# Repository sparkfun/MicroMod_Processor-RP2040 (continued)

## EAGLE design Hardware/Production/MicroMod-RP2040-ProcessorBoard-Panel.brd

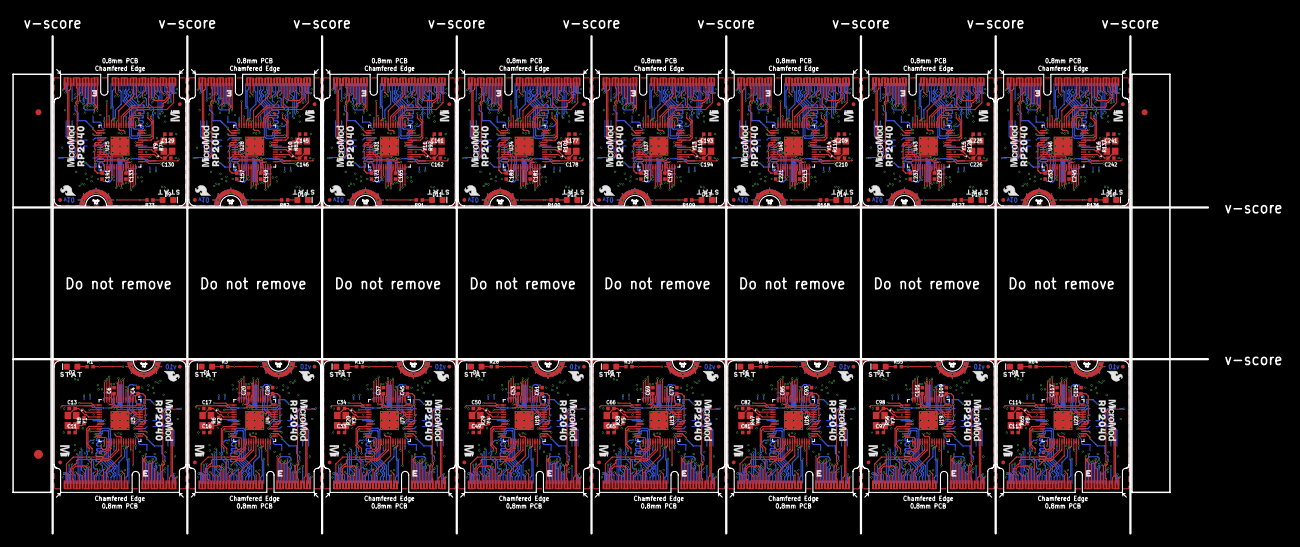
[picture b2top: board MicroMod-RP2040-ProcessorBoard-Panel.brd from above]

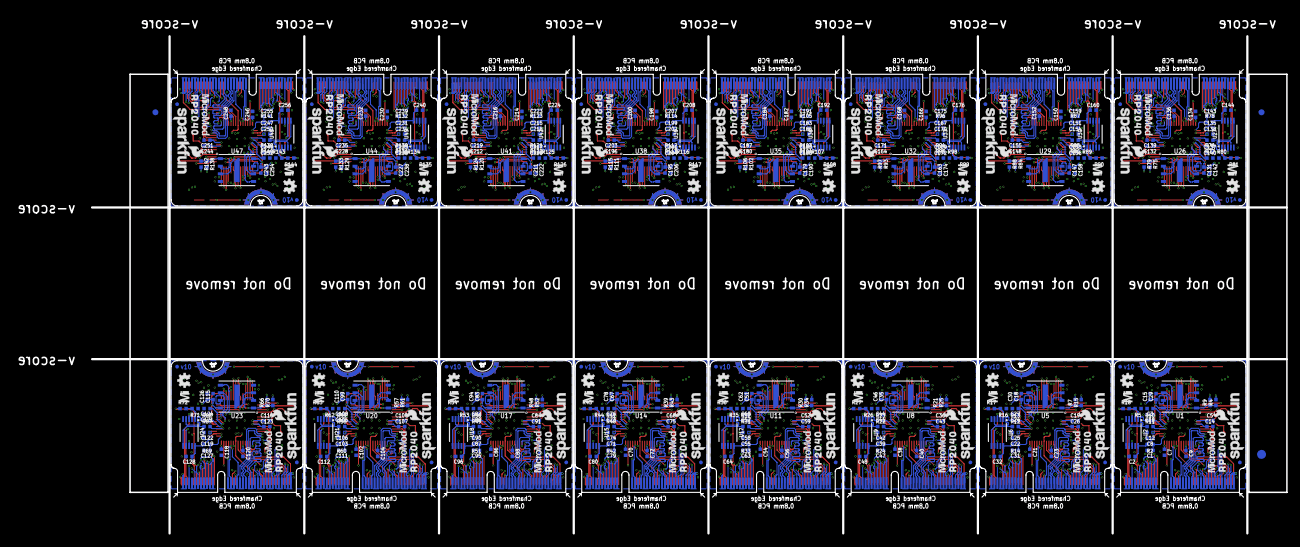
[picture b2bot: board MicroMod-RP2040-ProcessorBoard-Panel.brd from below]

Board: 4 copper layers, 199.6 x 83.1 mm, 726 parts (451 on the bottom side), 928 nets.

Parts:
C1, C3, C4, C15, C27, C28, C30, C31, C44, C45, C46, C47, C60, C61, C62, C63, C76, C77, C78, C79, C92, C93, C94, C95, C108, C109, C110, C111, C124, C125, C126, C127, C140, C141, C142, C143, C156, C157, C158, C159, C172, C173, C174, C175, C188, C189, C190, C191, C204, C205, C206, C207, C220, C221, C222, C223, C236, C237, C238, C239, C252, C253, C254, C255: 2.2uF; 0402-TIGHT
C2, C5, C6, C7, C8, C9, C10, C12, C14, C18, C19, C20, C21, C22, C23, C24, C25, C26, C29, C32, C35, C36, C37, C38, C39, C40, C41, C42, C43, C48, C51, C52, C53, C54, C55, C56, C57, C58, C59, C64, C67, C68, C69, C70, C71, C72, C73, C74, C75, C80, C83, C84, C85, C86, C87, C88, C89, C90, C91, C96, C99, C100, C101, C102, C103, C104, C105, C106, C107, C112, C115, C116, C117, C118, C119, C120, C121, C122, C123, C128, C131, C132, C133, C134, C135, C136, C137, C138, C139, C144, C147, C148, C149, C150, C151, C152, C153, C154, C155, C160, C163, C164, C165, C166, C167, C168, C169, C170, C171, C176, C179, C180, C181, C182, C183, C184, C185, C186, C187, C192, C195, C196, C197, C198, C199, C200, C201, C202, C203, C208, C211, C212, C213, C214, C215, C216, C217, C218, C219, C224, C227, C228, C229, C230, C231, C232, C233, C234, C235, C240, C243, C244, C245, C246, C247, C248, C249, C250, C251, C256: 0.1uF; 0402-TIGHT
C11, C13, C16, C17, C33, C34, C49, C50, C65, C66, C81, C82, C97, C98, C113, C114, C129, C130, C145, C146, C161, C162, C177, C178, C193, C194, C209, C210, C225, C226, C241, C242: 15pF; 0402-TIGHT
D1, D2, D3, D4, D5, D6, D7, D8, D9, D10, D11, D12, D13, D14, D15, D16: BLUE; LED-0603
E$1, E$2, E$3, E$4: FIDUCIAL-1X2
E$5, E$6: FIDUCIAL-1.5X3
FD1, FD2, FD3, FD4, FD5, FD6, FD7, FD8, FD9, FD10, FD11, FD12, FD13, FD14, FD15, FD16, FD17, FD18, FD19, FD20, FD21, FD22, FD23, FD24, FD25, FD26, FD27, FD28, FD29, FD30, FD31, FD32, FD33, FD34, FD35, FD36, FD37, FD38, FD39, FD40, FD41, FD42, FD43, FD44, FD45, FD46, FD47, FD48, FD49, FD50, FD51, FD52, FD53, FD54, FD55, FD56, FD57, FD58, FD59, FD60, FD61, FD62, FD63, FD64: FIDUCIALUFIDUCIAL; FIDUCIAL-MICRO
J1, J2, J3, J4, J5, J6, J7, J8, J9, J10, J11, J12, J13, J14, J15, J16: MICROMOD-2222; M.2-CARD-E-22
LOGO1, LOGO5, LOGO8, LOGO11, LOGO14, LOGO17, LOGO20, LOGO23, LOGO26, LOGO29, LOGO32, LOGO35, LOGO38, LOGO41, LOGO44, LOGO47: SFE_LOGO_NAME_FLAME.1_INCH; SFE_LOGO_NAME_FLAME_.1
LOGO2, LOGO6, LOGO9, LOGO12, LOGO15, LOGO18, LOGO21, LOGO24, LOGO27, LOGO30, LOGO33, LOGO36, LOGO39, LOGO42, LOGO45, LOGO48: SFE_LOGO_FLAME.1_INCH; SFE_LOGO_FLAME_.1
LOGO3, LOGO4, LOGO7, LOGO10, LOGO13, LOGO16, LOGO19, LOGO22, LOGO25, LOGO28, LOGO31, LOGO34, LOGO37, LOGO40, LOGO43, LOGO46: OSHW-LOGOMINI; OSHW-LOGO-MINI
R1, R3, R6, R7, R8, R9, R17, R18, R19, R20, R21, R27, R28, R29, R30, R36, R37, R38, R39, R45, R46, R47, R48, R54, R55, R56, R57, R63, R64, R65, R66, R72, R73, R74, R75, R81, R82, R83, R84, R90, R91, R92, R93, R99, R100, R101, R102, R108, R109, R110, R111, R117, R118, R119, R120, R126, R127, R128, R129, R135, R136, R137, R138, R144: 1k; 0402-TIGHT
R2, R14, R24, R33, R42, R51, R60, R69, R78, R87, R96, R105, R114, R123, R132, R141: 200OHM-0402T-1/16W-1%; 0402-TIGHT
R4, R5, R15, R16, R25, R26, R34, R35, R43, R44, R52, R53, R61, R62, R70, R71, R79, R80, R88, R89, R97, R98, R106, R107, R115, R116, R124, R125, R133, R134, R142, R143: 10k; 0402-TIGHT
R10, R11, R12, R13, R22, R23, R31, R32, R40, R41, R49, R50, R58, R59, R67, R68, R76, R77, R85, R86, R94, R95, R103, R104, R112, R113, R121, R122, R130, R131, R139, R140: 27; 0402-TIGHT
U1, U5, U8, U11, U14, U17, U20, U23, U26, U29, U32, U35, U38, U41, U44, U47: W25QXX128MBIT; WSON-8-6X5-SKINNY_CENTERPAD
U2, U6, U9, U12, U15, U18, U21, U24, U27, U30, U33, U36, U39, U42, U45, U48: FSUSB30MUX_MSOP10; MSOP10
U3, U4, U7, U10, U13, U16, U19, U22, U25, U28, U31, U34, U37, U40, U43, U46: RP2040; QFN-56
U$1, U$2, U$5, U$7, U$15, U$16, U$22, U$23, U$29, U$30, U$36, U$37, U$43, U$44, U$50, U$51, U$57, U$58, U$64, U$65, U$71, U$72, U$78, U$79, U$85, U$86, U$92, U$93, U$99, U$100, U$106, U$107: MICROMOD_MI_LOGO_.35
U$3, U$10, U$12, U$13, U$19, U$20, U$26, U$27, U$33, U$34, U$40, U$41, U$47, U$48, U$54, U$55, U$61, U$62, U$68, U$69, U$75, U$76, U$82, U$83, U$89, U$90, U$96, U$97, U$103, U$104, U$110, U$111: MICROMOD_LOGO_.3
U$4, U$8, U$9, U$14, U$18, U$21, U$25, U$28, U$32, U$35, U$39, U$42, U$46, U$49, U$53, U$56, U$60, U$63, U$67, U$70, U$74, U$77, U$81, U$84, U$88, U$91, U$95, U$98, U$102, U$105, U$109, U$112: RP20400
U$6, U$11, U$17, U$24, U$31, U$38, U$45, U$52, U$59, U$66, U$73, U$80, U$87, U$94, U$101, U$108: STAT0
Y1, Y2, Y3, Y4, Y5, Y6, Y7, Y8, Y9, Y10, Y11, Y12, Y13, Y14, Y15, Y16: 12MHz; CRYSTAL-SMD-2X2.5MM

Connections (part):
1.1V: C3.1, C12.1, C14.1, U3.23, U3.45, U3.50
1.1V1: C25.1, C26.1, C27.1, U4.23, U4.45, U4.50
1.1V2: C42.1, C43.1, C44.1, U7.23, U7.45, U7.50
1.1V3: C58.1, C59.1, C60.1, U10.23, U10.45, U10.50
1.1V4: C74.1, C75.1, C76.1, U13.23, U13.45, U13.50
1.1V5: C90.1, C91.1, C92.1, U16.23, U16.45, U16.50
1.1V6: C106.1, C107.1, C108.1, U19.23, U19.45, U19.50
1.1V7: C122.1, C123.1, C124.1, U22.23, U22.45, U22.50
1.1V8: C138.1, C139.1, C140.1, U25.23, U25.45, U25.50
1.1V9: C154.1, C155.1, C156.1, U28.23, U28.45, U28.50
1.1V10: C170.1, C171.1, C172.1, U31.23, U31.45, U31.50
1.1V11: C186.1, C187.1, C188.1, U34.23, U34.45, U34.50
1.1V12: C202.1, C203.1, C204.1, U37.23, U37.45, U37.50
1.1V13: C218.1, C219.1, C220.1, U40.23, U40.45, U40.50
1.1V14: C234.1, C235.1, C236.1, U43.23, U43.45, U43.50
1.1V15: C250.1, C251.1, C252.1, U46.23, U46.45, U46.50
3.3V: C2.1, C4.1, C5.1, C6.1, C7.1, C8.1, C9.1, C10.1, C15.1, C29.1, J1.2, J1.72, J1.74, R2.2, R4.2, U1.8, U2.10, U3.1, U3.10, U3.22, U3.33, U3.42, U3.44, U3.48, U3.49
3.3V1: C18.1, C19.1, C20.1, C21.1, C22.1, C23.1, C24.1, C28.1, C30.1, C32.1, J2.2, J2.72, J2.74, R14.2, R15.2, U4.1, U4.10, U4.22, U4.33, U4.42, U4.44, U4.48, U4.49, U5.8, U6.10
3.3V2: C35.1, C36.1, C37.1, C38.1, C39.1, C40.1, C41.1, C45.1, C46.1, C48.1, J3.2, J3.72, J3.74, R24.2, R25.2, U7.1, U7.10, U7.22, U7.33, U7.42, U7.44, U7.48, U7.49, U8.8, U9.10
3.3V3: C51.1, C52.1, C53.1, C54.1, C55.1, C56.1, C57.1, C61.1, C62.1, C64.1, J4.2, J4.72, J4.74, R33.2, R34.2, U10.1, U10.10, U10.22, U10.33, U10.42, U10.44, U10.48, U10.49, U11.8, U12.10
3.3V4: C67.1, C68.1, C69.1, C70.1, C71.1, C72.1, C73.1, C77.1, C78.1, C80.1, J5.2, J5.72, J5.74, R42.2, R43.2, U13.1, U13.10, U13.22, U13.33, U13.42, U13.44, U13.48, U13.49, U14.8, U15.10
3.3V5: C83.1, C84.1, C85.1, C86.1, C87.1, C88.1, C89.1, C93.1, C94.1, C96.1, J6.2, J6.72, J6.74, R51.2, R52.2, U16.1, U16.10, U16.22, U16.33, U16.42, U16.44, U16.48, U16.49, U17.8, U18.10
3.3V6: C99.1, C100.1, C101.1, C102.1, C103.1, C104.1, C105.1, C109.1, C110.1, C112.1, J7.2, J7.72, J7.74, R60.2, R61.2, U19.1, U19.10, U19.22, U19.33, U19.42, U19.44, U19.48, U19.49, U20.8, U21.10
3.3V7: C115.1, C116.1, C117.1, C118.1, C119.1, C120.1, C121.1, C125.1, C126.1, C128.1, J8.2, J8.72, J8.74, R69.2, R70.2, U22.1, U22.10, U22.22, U22.33, U22.42, U22.44, U22.48, U22.49, U23.8, U24.10
3.3V8: C131.1, C132.1, C133.1, C134.1, C135.1, C136.1, C137.1, C141.1, C142.1, C144.1, J9.2, J9.72, J9.74, R78.2, R79.2, U25.1, U25.10, U25.22, U25.33, U25.42, U25.44, U25.48, U25.49, U26.8, U27.10
3.3V9: C147.1, C148.1, C149.1, C150.1, C151.1, C152.1, C153.1, C157.1, C158.1, C160.1, J10.2, J10.72, J10.74, R87.2, R88.2, U28.1, U28.10, U28.22, U28.33, U28.42, U28.44, U28.48, U28.49, U29.8, U30.10
3.3V10: C163.1, C164.1, C165.1, C166.1, C167.1, C168.1, C169.1, C173.1, C174.1, C176.1, J11.2, J11.72, J11.74, R96.2, R97.2, U31.1, U31.10, U31.22, U31.33, U31.42, U31.44, U31.48, U31.49, U32.8, U33.10
3.3V11: C179.1, C180.1, C181.1, C182.1, C183.1, C184.1, C185.1, C189.1, C190.1, C192.1, J12.2, J12.72, J12.74, R105.2, R106.2, U34.1, U34.10, U34.22, U34.33, U34.42, U34.44, U34.48, U34.49, U35.8, U36.10
3.3V12: C195.1, C196.1, C197.1, C198.1, C199.1, C200.1, C201.1, C205.1, C206.1, C208.1, J13.2, J13.72, J13.74, R114.2, R115.2, U37.1, U37.10, U37.22, U37.33, U37.42, U37.44, U37.48, U37.49, U38.8, U39.10
3.3V13: C211.1, C212.1, C213.1, C214.1, C215.1, C216.1, C217.1, C221.1, C222.1, C224.1, J14.2, J14.72, J14.74, R123.2, R124.2, U40.1, U40.10, U40.22, U40.33, U40.42, U40.44, U40.48, U40.49, U41.8, U42.10
3.3V14: C227.1, C228.1, C229.1, C230.1, C231.1, C232.1, C233.1, C237.1, C238.1, C240.1, J15.2, J15.72, J15.74, R132.2, R133.2, U43.1, U43.10, U43.22, U43.33, U43.42, U43.44, U43.48, U43.49, U44.8, U45.10
3.3V15: C243.1, C244.1, C245.1, C246.1, C247.1, C248.1, C249.1, C253.1, C254.1, C256.1, J16.2, J16.72, J16.74, R141.2, R142.2, U46.1, U46.10, U46.22, U46.33, U46.42, U46.44, U46.48, U46.49, U47.8, U48.10
!RESET!: J1.6, U3.26
!RESET!1: J2.6, U4.26
!RESET!2: J3.6, U7.26
!RESET!3: J4.6, U10.26
!RESET!4: J5.6, U13.26
!RESET!5: J6.6, U16.26
!RESET!6: J7.6, U19.26
!RESET!7: J8.6, U22.26
!RESET!8: J9.6, U25.26
!RESET!9: J10.6, U28.26
!RESET!10: J11.6, U31.26
!RESET!11: J12.6, U34.26
!RESET!12: J13.6, U37.26
!RESET!13: J14.6, U40.26
!RESET!14: J15.6, U43.26
!RESET!15: J16.6, U46.26
ADC0: J1.34, U3.38
ADC1: J1.38, U3.39
ADC2: J2.34, U4.38
ADC3: J2.38, U4.39
ADC4: J3.34, U7.38
ADC5: J3.38, U7.39
ADC6: J4.34, U10.38
ADC7: J4.38, U10.39
ADC8: J5.34, U13.38
ADC9: J5.38, U13.39
ADC10: J6.34, U16.38
ADC11: J6.38, U16.39
ADC12: J7.34, U19.38
ADC13: J7.38, U19.39
ADC14: J8.34, U22.38
ADC15: J8.38, U22.39
ADC16: J9.34, U25.38
ADC17: J9.38, U25.39
ADC18: J10.34, U28.38
ADC19: J10.38, U28.39
ADC20: J11.34, U31.38
ADC21: J11.38, U31.39
ADC22: J12.34, U34.38
ADC23: J12.38, U34.39
ADC24: J13.34, U37.38
ADC25: J13.38, U37.39
ADC26: J14.34, U40.38
ADC27: J14.38, U40.39
ADC28: J15.34, U43.38
ADC29: J15.38, U43.39
ADC30: J16.34, U46.38
ADC31: J16.38, U46.39
ADC_VDD: C1.1, R2.1, U3.43
ADC_VDD1: C31.1, R14.1, U4.43
ADC_VDD2: C47.1, R24.1, U7.43
ADC_VDD3: C63.1, R33.1, U10.43
ADC_VDD4: C79.1, R42.1, U13.43
ADC_VDD5: C95.1, R51.1, U16.43
ADC_VDD6: C111.1, R60.1, U19.43
ADC_VDD7: C127.1, R69.1, U22.43
ADC_VDD8: C143.1, R78.1, U25.43
ADC_VDD9: C159.1, R87.1, U28.43
ADC_VDD10: C175.1, R96.1, U31.43
ADC_VDD11: C191.1, R105.1, U34.43
ADC_VDD12: C207.1, R114.1, U37.43
ADC_VDD13: C223.1, R123.1, U40.43
ADC_VDD14: C239.1, R132.1, U43.43
ADC_VDD15: C255.1, R141.1, U46.43
BATT_VIN/1: J2.49, U4.41
BATT_VIN/2: J3.49, U7.41
BATT_VIN/3: J1.49, U3.41
BATT_VIN/4: J4.49, U10.41
BATT_VIN/5: J5.49, U13.41
BATT_VIN/6: J6.49, U16.41
BATT_VIN/7: J7.49, U19.41
BATT_VIN/8: J8.49, U22.41
BATT_VIN/9: J9.49, U25.41
BATT_VIN/10: J10.49, U28.41
BATT_VIN/11: J11.49, U31.41
BATT_VIN/12: J12.49, U34.41
BATT_VIN/13: J13.49, U37.41
BATT_VIN/14: J14.49, U40.41
BATT_VIN/15: J15.49, U43.41
BATT_VIN/16: J16.49, U46.41
BOOT: J1.11, R9.2
BOOT1: J2.11, R7.2
BOOT2: J3.11, R21.2
BOOT3: J4.11, R30.2
BOOT4: J5.11, R39.2
BOOT5: J6.11, R48.2
BOOT6: J7.11, R57.2
BOOT7: J8.11, R66.2
BOOT8: J9.11, R75.2
BOOT9: J10.11, R84.2
BOOT10: J11.11, R93.2
BOOT11: J12.11, R102.2
BOOT12: J13.11, R111.2
BOOT13: J14.11, R120.2
BOOT14: J15.11, R129.2
BOOT15: J16.11, R138.2
CTS1/AUD_LRCLK: J1.15, J1.52, U3.4
CTS1/AUD_LRCLK1: J2.15, J2.52, U4.4
CTS1/AUD_LRCLK2: J3.15, J3.52, U7.4
CTS1/AUD_LRCLK3: J4.15, J4.52, U10.4
CTS1/AUD_LRCLK4: J5.15, J5.52, U13.4
CTS1/AUD_LRCLK5: J6.15, J6.52, U16.4
CTS1/AUD_LRCLK6: J7.15, J7.52, U19.4
CTS1/AUD_LRCLK7: J8.15, J8.52, U22.4
CTS1/AUD_LRCLK8: J9.15, J9.52, U25.4
CTS1/AUD_LRCLK9: J10.15, J10.52, U28.4
CTS1/AUD_LRCLK10: J11.15, J11.52, U31.4
CTS1/AUD_LRCLK11: J12.15, J12.52, U34.4
CTS1/AUD_LRCLK12: J13.15, J13.52, U37.4
CTS1/AUD_LRCLK13: J14.15, J14.52, U40.4
CTS1/AUD_LRCLK14: J15.15, J15.52, U43.4
CTS1/AUD_LRCLK15: J16.15, J16.52, U46.4
D0: J1.10, U3.8
D1: J1.18, U3.9
D2: J2.10, U4.8
D3: J2.18, U4.9
D4: J3.10, U7.8
D5: J3.18, U7.9
D6: J4.10, U10.8
D7: J4.18, U10.9
D8: J5.10, U13.8
D9: J5.18, U13.9
D10: J6.10, U16.8
D11: J6.18, U16.9
D12: J7.10, U19.8
D13: J7.18, U19.9
D14: J8.10, U22.8
D15: J8.18, U22.9
D16: J9.10, U25.8
D17: J9.18, U25.9
D18: J10.10, U28.8
D19: J10.18, U28.9
D20: J11.10, U31.8
D21: J11.18, U31.9
D22: J12.10, U34.8
D23: J12.18, U34.9
D24: J13.10, U37.8
D25: J13.18, U37.9
D26: J14.10, U40.8
D27: J14.18, U40.9
D28: J15.10, U43.8
D29: J15.18, U43.9
D30: J16.10, U46.8
D31: J16.18, U46.9
GND: C1.2, C2.2, C3.2, C4.2, C5.2, C6.2, C7.2, C8.2, C9.2, C10.2, C11.1, C12.2, C13.1, C14.2, C15.2, C29.2, D2.C, J1.1, J1.7, J1.33, J1.36, J1.39, J1.45, J1.75, J1.GND1, J1.GND2, J1.GND3, R5.1, U1.4, U2.5, U2.9, U3.19, U3.EPAD
GND1: C16.1, C17.1, C18.2, C19.2, C20.2, C21.2, C22.2, C23.2, C24.2, C25.2, C26.2, C27.2, C28.2, C30.2, C31.2, C32.2, D1.C, J2.1, J2.7, J2.33, J2.36, J2.39, J2.45, J2.75, J2.GND1, J2.GND2, J2.GND3, R16.1, U4.19, U4.EPAD, U5.4, U6.5, U6.9
GND2: C33.1, C34.1, C35.2, C36.2, C37.2, C38.2, C39.2, C40.2, C41.2, C42.2, C43.2, C44.2, C45.2, C46.2, C47.2, C48.2, D3.C, J3.1, J3.7, J3.33, J3.36, J3.39, J3.45, J3.75, J3.GND1, J3.GND2, J3.GND3, R26.1, U7.19, U7.EPAD, U8.4, U9.5, U9.9
GND3: C49.1, C50.1, C51.2, C52.2, C53.2, C54.2, C55.2, C56.2, C57.2, C58.2, C59.2, C60.2, C61.2, C62.2, C63.2, C64.2, D4.C, J4.1, J4.7, J4.33, J4.36, J4.39, J4.45, J4.75, J4.GND1, J4.GND2, J4.GND3, R35.1, U10.19, U10.EPAD, U11.4, U12.5, U12.9
GND4: C65.1, C66.1, C67.2, C68.2, C69.2, C70.2, C71.2, C72.2, C73.2, C74.2, C75.2, C76.2, C77.2, C78.2, C79.2, C80.2, D5.C, J5.1, J5.7, J5.33, J5.36, J5.39, J5.45, J5.75, J5.GND1, J5.GND2, J5.GND3, R44.1, U13.19, U13.EPAD, U14.4, U15.5, U15.9
GND5: C81.1, C82.1, C83.2, C84.2, C85.2, C86.2, C87.2, C88.2, C89.2, C90.2, C91.2, C92.2, C93.2, C94.2, C95.2, C96.2, D6.C, J6.1, J6.7, J6.33, J6.36, J6.39, J6.45, J6.75, J6.GND1, J6.GND2, J6.GND3, R53.1, U16.19, U16.EPAD, U17.4, U18.5, U18.9
GND6: C97.1, C98.1, C99.2, C100.2, C101.2, C102.2, C103.2, C104.2, C105.2, C106.2, C107.2, C108.2, C109.2, C110.2, C111.2, C112.2, D7.C, J7.1, J7.7, J7.33, J7.36, J7.39, J7.45, J7.75, J7.GND1, J7.GND2, J7.GND3, R62.1, U19.19, U19.EPAD, U20.4, U21.5, U21.9
GND7: C113.1, C114.1, C115.2, C116.2, C117.2, C118.2, C119.2, C120.2, C121.2, C122.2, C123.2, C124.2, C125.2, C126.2, C127.2, C128.2, D8.C, J8.1, J8.7, J8.33, J8.36, J8.39, J8.45, J8.75, J8.GND1, J8.GND2, J8.GND3, R71.1, U22.19, U22.EPAD, U23.4, U24.5, U24.9
GND8: C129.1, C130.1, C131.2, C132.2, C133.2, C134.2, C135.2, C136.2, C137.2, C138.2, C139.2, C140.2, C141.2, C142.2, C143.2, C144.2, D9.C, J9.1, J9.7, J9.33, J9.36, J9.39, J9.45, J9.75, J9.GND1, J9.GND2, J9.GND3, R80.1, U25.19, U25.EPAD, U26.4, U27.5, U27.9
GND9: C145.1, C146.1, C147.2, C148.2, C149.2, C150.2, C151.2, C152.2, C153.2, C154.2, C155.2, C156.2, C157.2, C158.2, C159.2, C160.2, D10.C, J10.1, J10.7, J10.33, J10.36, J10.39, J10.45, J10.75, J10.GND1, J10.GND2, J10.GND3, R89.1, U28.19, U28.EPAD, U29.4, U30.5, U30.9
GND10: C161.1, C162.1, C163.2, C164.2, C165.2, C166.2, C167.2, C168.2, C169.2, C170.2, C171.2, C172.2, C173.2, C174.2, C175.2, C176.2, D11.C, J11.1, J11.7, J11.33, J11.36, J11.39, J11.45, J11.75, J11.GND1, J11.GND2, J11.GND3, R98.1, U31.19, U31.EPAD, U32.4, U33.5, U33.9
GND11: C177.1, C178.1, C179.2, C180.2, C181.2, C182.2, C183.2, C184.2, C185.2, C186.2, C187.2, C188.2, C189.2, C190.2, C191.2, C192.2, D12.C, J12.1, J12.7, J12.33, J12.36, J12.39, J12.45, J12.75, J12.GND1, J12.GND2, J12.GND3, R107.1, U34.19, U34.EPAD, U35.4, U36.5, U36.9
GND12: C193.1, C194.1, C195.2, C196.2, C197.2, C198.2, C199.2, C200.2, C201.2, C202.2, C203.2, C204.2, C205.2, C206.2, C207.2, C208.2, D13.C, J13.1, J13.7, J13.33, J13.36, J13.39, J13.45, J13.75, J13.GND1, J13.GND2, J13.GND3, R116.1, U37.19, U37.EPAD, U38.4, U39.5, U39.9
GND13: C209.1, C210.1, C211.2, C212.2, C213.2, C214.2, C215.2, C216.2, C217.2, C218.2, C219.2, C220.2, C221.2, C222.2, C223.2, C224.2, D14.C, J14.1, J14.7, J14.33, J14.36, J14.39, J14.45, J14.75, J14.GND1, J14.GND2, J14.GND3, R125.1, U40.19, U40.EPAD, U41.4, U42.5, U42.9
GND14: C225.1, C226.1, C227.2, C228.2, C229.2, C230.2, C231.2, C232.2, C233.2, C234.2, C235.2, C236.2, C237.2, C238.2, C239.2, C240.2, D15.C, J15.1, J15.7, J15.33, J15.36, J15.39, J15.45, J15.75, J15.GND1, J15.GND2, J15.GND3, R134.1, U43.19, U43.EPAD, U44.4, U45.5, U45.9
GND15: C241.1, C242.1, C243.2, C244.2, C245.2, C246.2, C247.2, C248.2, C249.2, C250.2, C251.2, C252.2, C253.2, C254.2, C255.2, C256.2, D16.C, J16.1, J16.7, J16.33, J16.36, J16.39, J16.45, J16.75, J16.GND1, J16.GND2, J16.GND3, R143.1, U46.19, U46.EPAD, U47.4, U48.5, U48.9
GPIO0: J1.40, U3.27
GPIO1: J1.42, U3.28
GPIO2: J1.44, U3.29
GPIO3: J1.46, U3.30
GPIO4: J2.42, U4.28
GPIO5: J2.46, U4.30
GPIO6: J2.44, U4.29
GPIO7: J2.40, U4.27
GPIO8: J2.65, U4.40
GPIO9: J1.65, U3.40
GPIO10: J3.42, U7.28
GPIO11: J3.46, U7.30
GPIO12: J3.44, U7.29
GPIO13: J3.40, U7.27
GPIO14: J3.65, U7.40
GPIO15: J4.42, U10.28
GPIO16: J4.46, U10.30
GPIO17: J4.44, U10.29
GPIO18: J4.40, U10.27
GPIO19: J4.65, U10.40
GPIO20: J5.42, U13.28
GPIO21: J5.46, U13.30
GPIO22: J5.44, U13.29
GPIO23: J5.40, U13.27
GPIO24: J5.65, U13.40
GPIO25: J6.42, U16.28
GPIO26: J6.46, U16.30
GPIO27: J6.44, U16.29
GPIO28: J6.40, U16.27
GPIO29: J6.65, U16.40
GPIO30: J7.42, U19.28
GPIO31: J7.46, U19.30
GPIO32: J7.44, U19.29
GPIO33: J7.40, U19.27
GPIO34: J7.65, U19.40
GPIO35: J8.42, U22.28
GPIO36: J8.46, U22.30
GPIO37: J8.44, U22.29
GPIO38: J8.40, U22.27
GPIO39: J8.65, U22.40
GPIO40: J9.42, U25.28
GPIO41: J9.46, U25.30
GPIO42: J9.44, U25.29
GPIO43: J9.40, U25.27
GPIO44: J9.65, U25.40
GPIO45: J10.42, U28.28
GPIO46: J10.46, U28.30
GPIO47: J10.44, U28.29
GPIO48: J10.40, U28.27
GPIO49: J10.65, U28.40
GPIO50: J11.42, U31.28
GPIO51: J11.46, U31.30
GPIO52: J11.44, U31.29
GPIO53: J11.40, U31.27
GPIO54: J11.65, U31.40
GPIO55: J12.42, U34.28
GPIO56: J12.46, U34.30
GPIO57: J12.44, U34.29
GPIO58: J12.40, U34.27
GPIO59: J12.65, U34.40
GPIO60: J13.42, U37.28
GPIO61: J13.46, U37.30
GPIO62: J13.44, U37.29
GPIO63: J13.40, U37.27
GPIO64: J13.65, U37.40
GPIO65: J14.42, U40.28
GPIO66: J14.46, U40.30
GPIO67: J14.44, U40.29
GPIO68: J14.40, U40.27
GPIO69: J14.65, U40.40
GPIO70: J15.42, U43.28
GPIO71: J15.46, U43.30
GPIO72: J15.44, U43.29
GPIO73: J15.40, U43.27
GPIO74: J15.65, U43.40
GPIO75: J16.42, U46.28
GPIO76: J16.46, U46.30
GPIO77: J16.44, U46.29
GPIO78: J16.40, U46.27
GPIO79: J16.65, U46.40
I2C_!INT!/TX1: J2.16, J2.22, U4.11
I2C_!INT!/TX2: J1.16, J1.22, U3.11
I2C_!INT!/TX3: J3.16, J3.22, U7.11
I2C_!INT!/TX4: J4.16, J4.22, U10.11
I2C_!INT!/TX5: J5.16, J5.22, U13.11
I2C_!INT!/TX6: J6.16, J6.22, U16.11
I2C_!INT!/TX7: J7.16, J7.22, U19.11
I2C_!INT!/TX8: J8.16, J8.22, U22.11
I2C_!INT!/TX9: J9.16, J9.22, U25.11
I2C_!INT!/TX10: J10.16, J10.22, U28.11
I2C_!INT!/TX11: J11.16, J11.22, U31.11
I2C_!INT!/TX12: J12.16, J12.22, U34.11
I2C_!INT!/TX13: J13.16, J13.22, U37.11
I2C_!INT!/TX14: J14.16, J14.22, U40.11
I2C_!INT!/TX15: J15.16, J15.22, U43.11
I2C_!INT!/TX16: J16.16, J16.22, U46.11
LED_BUILTIN/G1: J2.63, R3.2, U4.37
LED_BUILTIN/G2: J3.63, R19.2, U7.37
LED_BUILTIN/G3: J4.63, R28.2, U10.37
LED_BUILTIN/G4: J5.63, R37.2, U13.37
LED_BUILTIN/G5: J6.63, R46.2, U16.37
LED_BUILTIN/G6: J7.63, R55.2, U19.37
LED_BUILTIN/G7: J8.63, R64.2, U22.37
LED_BUILTIN/G8: J9.63, R73.2, U25.37
LED_BUILTIN/G9: J10.63, R82.2, U28.37
LED_BUILTIN/G10: J1.63, R1.2, U3.37
LED_BUILTIN/G11: J11.63, R91.2, U31.37
LED_BUILTIN/G12: J12.63, R100.2, U34.37
LED_BUILTIN/G13: J13.63, R109.2, U37.37
LED_BUILTIN/G14: J14.63, R118.2, U40.37
LED_BUILTIN/G15: J15.63, R127.2, U43.37
LED_BUILTIN/G16: J16.63, R136.2, U46.37
unnamed: D1.A, R3.1
unnamed: D2.A, R1.1
unnamed: R6.2, U4.21
unnamed: R8.2, U3.21
unnamed: C13.2, U3.20, Y1.P3
unnamed: C11.2, R8.1, Y1.P1
unnamed: C17.2, U4.20, Y2.P3
unnamed: C16.2, R6.1, Y2.P1
unnamed: D3.A, R19.1
unnamed: R20.2, U7.21
unnamed: C34.2, U7.20, Y3.P3
unnamed: C33.2, R20.1, Y3.P1
unnamed: D4.A, R28.1
unnamed: R29.2, U10.21
unnamed: C50.2, U10.20, Y4.P3
unnamed: C49.2, R29.1, Y4.P1
unnamed: D5.A, R37.1
unnamed: R38.2, U13.21
unnamed: C66.2, U13.20, Y5.P3
unnamed: C65.2, R38.1, Y5.P1
unnamed: D6.A, R46.1
unnamed: R47.2, U16.21
unnamed: C82.2, U16.20, Y6.P3
unnamed: C81.2, R47.1, Y6.P1
unnamed: D7.A, R55.1
unnamed: R56.2, U19.21
unnamed: C98.2, U19.20, Y7.P3
unnamed: C97.2, R56.1, Y7.P1
unnamed: D8.A, R64.1
unnamed: R65.2, U22.21
unnamed: C114.2, U22.20, Y8.P3
unnamed: C113.2, R65.1, Y8.P1
unnamed: D9.A, R73.1
unnamed: R74.2, U25.21
unnamed: C130.2, U25.20, Y9.P3
unnamed: C129.2, R74.1, Y9.P1
unnamed: D10.A, R82.1
unnamed: R83.2, U28.21
unnamed: C146.2, U28.20, Y10.P3
unnamed: C145.2, R83.1, Y10.P1
unnamed: D11.A, R91.1
unnamed: R92.2, U31.21
unnamed: C162.2, U31.20, Y11.P3
unnamed: C161.2, R92.1, Y11.P1
unnamed: D12.A, R100.1
unnamed: R101.2, U34.21
unnamed: C178.2, U34.20, Y12.P3
unnamed: C177.2, R101.1, Y12.P1
unnamed: D13.A, R109.1
unnamed: R110.2, U37.21
unnamed: C194.2, U37.20, Y13.P3
unnamed: C193.2, R110.1, Y13.P1
unnamed: D14.A, R118.1
unnamed: R119.2, U40.21
unnamed: C210.2, U40.20, Y14.P3
unnamed: C209.2, R119.1, Y14.P1
unnamed: D15.A, R127.1
unnamed: R128.2, U43.21
unnamed: C226.2, U43.20, Y15.P3
unnamed: C225.2, R128.1, Y15.P1
unnamed: D16.A, R136.1
unnamed: R137.2, U46.21
unnamed: C242.2, U46.20, Y16.P3
unnamed: C241.2, R137.1, Y16.P1
PWM0: J1.32, U3.16
PWM1: J2.32, U4.16
PWM1/AUD_MCLK: J1.47, J1.58, U3.36
PWM1/AUD_MCLK1: J2.47, J2.58, U4.36
PWM1/AUD_MCLK2: J3.47, J3.58, U7.36
PWM1/AUD_MCLK3: J4.47, J4.58, U10.36
PWM1/AUD_MCLK4: J5.47, J5.58, U13.36
PWM1/AUD_MCLK5: J6.47, J6.58, U16.36
PWM1/AUD_MCLK6: J7.47, J7.58, U19.36
PWM1/AUD_MCLK7: J8.47, J8.58, U22.36
PWM1/AUD_MCLK8: J9.47, J9.58, U25.36
PWM1/AUD_MCLK9: J10.47, J10.58, U28.36
PWM1/AUD_MCLK10: J11.47, J11.58, U31.36
PWM1/AUD_MCLK11: J12.47, J12.58, U34.36
PWM1/AUD_MCLK12: J13.47, J13.58, U37.36
PWM1/AUD_MCLK13: J14.47, J14.58, U40.36
PWM1/AUD_MCLK14: J15.47, J15.58, U43.36
PWM1/AUD_MCLK15: J16.47, J16.58, U46.36
PWM2: J3.32, U7.16
PWM3: J4.32, U10.16
PWM4: J5.32, U13.16
PWM5: J6.32, U16.16
PWM6: J7.32, U19.16
PWM7: J8.32, U22.16
PWM8: J9.32, U25.16
PWM9: J10.32, U28.16
PWM10: J11.32, U31.16
PWM11: J12.32, U34.16
PWM12: J13.32, U37.16
PWM13: J14.32, U40.16
PWM14: J15.32, U43.16
PWM15: J16.32, U46.16
QSPI-0: U1.5, U3.53
QSPI-1: U1.2, U3.55
QSPI-2: U1.3, U3.54
QSPI-3: U1.7, U3.51
QSPI-4: U4.53, U5.5
QSPI-5: U4.51, U5.7
QSPI-6: U4.55, U5.2
QSPI-7: U4.54, U5.3
QSPI-8: U7.53, U8.5
QSPI-9: U7.51, U8.7
QSPI-10: U7.55, U8.2
QSPI-11: U7.54, U8.3
QSPI-12: U10.53, U11.5
QSPI-13: U10.51, U11.7
QSPI-14: U10.55, U11.2
QSPI-15: U10.54, U11.3
QSPI-16: U13.53, U14.5
QSPI-17: U13.51, U14.7
QSPI-18: U13.55, U14.2
QSPI-19: U13.54, U14.3
QSPI-20: U16.53, U17.5
QSPI-21: U16.51, U17.7
QSPI-22: U16.55, U17.2
QSPI-23: U16.54, U17.3
QSPI-24: U19.53, U20.5
QSPI-25: U19.51, U20.7
QSPI-26: U19.55, U20.2
QSPI-27: U19.54, U20.3
QSPI-28: U22.53, U23.5
QSPI-29: U22.51, U23.7
QSPI-30: U22.55, U23.2
QSPI-31: U22.54, U23.3
QSPI-32: U25.53, U26.5
QSPI-33: U25.51, U26.7
QSPI-34: U25.55, U26.2
QSPI-35: U25.54, U26.3
QSPI-36: U28.53, U29.5
QSPI-37: U28.51, U29.7
QSPI-38: U28.55, U29.2
QSPI-39: U28.54, U29.3
QSPI-40: U31.53, U32.5
QSPI-41: U31.51, U32.7
QSPI-42: U31.55, U32.2
QSPI-43: U31.54, U32.3
QSPI-44: U34.53, U35.5
QSPI-45: U34.51, U35.7
QSPI-46: U34.55, U35.2
QSPI-47: U34.54, U35.3
QSPI-48: U37.53, U38.5
QSPI-49: U37.51, U38.7
QSPI-50: U37.55, U38.2
QSPI-51: U37.54, U38.3
QSPI-52: U40.53, U41.5
QSPI-53: U40.51, U41.7
QSPI-54: U40.55, U41.2
QSPI-55: U40.54, U41.3
QSPI-56: U43.53, U44.5
QSPI-57: U43.51, U44.7
QSPI-58: U43.55, U44.2
QSPI-59: U43.54, U44.3
QSPI-60: U46.53, U47.5
QSPI-61: U46.51, U47.7
QSPI-62: U46.55, U47.2
QSPI-63: U46.54, U47.3
QSPI-CLK: U1.6, U3.52
QSPI-CLK1: U4.52, U5.6
QSPI-CLK2: U7.52, U8.6
QSPI-CLK3: U10.52, U11.6
QSPI-CLK4: U13.52, U14.6
QSPI-CLK5: U16.52, U17.6
QSPI-CLK6: U19.52, U20.6
QSPI-CLK7: U22.52, U23.6
QSPI-CLK8: U25.52, U26.6
QSPI-CLK9: U28.52, U29.6
QSPI-CLK10: U31.52, U32.6
QSPI-CLK11: U34.52, U35.6
QSPI-CLK12: U37.52, U38.6
QSPI-CLK13: U40.52, U41.6
QSPI-CLK14: U43.52, U44.6
QSPI-CLK15: U46.52, U47.6
QSPI-CS: R4.1, R9.1, U1.1, U3.56
QSPI-CS1: R7.1, R15.1, U4.56, U5.1
QSPI-CS2: R21.1, R25.1, U7.56, U8.1
QSPI-CS3: R30.1, R34.1, U10.56, U11.1
QSPI-CS4: R39.1, R43.1, U13.56, U14.1
QSPI-CS5: R48.1, R52.1, U16.56, U17.1
QSPI-CS6: R57.1, R61.1, U19.56, U20.1
QSPI-CS7: R66.1, R70.1, U22.56, U23.1
QSPI-CS8: R75.1, R79.1, U25.56, U26.1
QSPI-CS9: R84.1, R88.1, U28.56, U29.1
QSPI-CS10: R93.1, R97.1, U31.56, U32.1
QSPI-CS11: R102.1, R106.1, U34.56, U35.1
QSPI-CS12: R111.1, R115.1, U37.56, U38.1
QSPI-CS13: R120.1, R124.1, U40.56, U41.1
QSPI-CS14: R129.1, R133.1, U43.56, U44.1
QSPI-CS15: R138.1, R142.1, U46.56, U47.1
RP_D1+: R10.2, U3.47
RP_D1+1: R13.2, U4.47
RP_D1+2: R23.2, U7.47
RP_D1+3: R32.2, U10.47
RP_D1+4: R41.2, U13.47
RP_D1+5: R50.2, U16.47
RP_D1+6: R59.2, U19.47
RP_D1+7: R68.2, U22.47
RP_D1+8: R77.2, U25.47
RP_D1+9: R86.2, U28.47
RP_D1+10: R95.2, U31.47
RP_D1+11: R104.2, U34.47
RP_D1+12: R113.2, U37.47
RP_D1+13: R122.2, U40.47
RP_D1+14: R131.2, U43.47
RP_D1+15: R140.2, U46.47
RP_D1-: R11.2, U3.46
RP_D1-1: R12.2, U4.46
RP_D1-2: R22.2, U7.46
RP_D1-3: R31.2, U10.46
RP_D1-4: R40.2, U13.46
RP_D1-5: R49.2, U16.46
RP_D1-6: R58.2, U19.46
RP_D1-7: R67.2, U22.46
RP_D1-8: R76.2, U25.46
RP_D1-9: R85.2, U28.46
RP_D1-10: R94.2, U31.46
RP_D1-11: R103.2, U34.46
RP_D1-12: R112.2, U37.46
RP_D1-13: R121.2, U40.46
RP_D1-14: R130.2, U43.46
RP_D1-15: R139.2, U46.46
RP_D+: R10.1, U2.4
RP_D+1: R13.1, U6.4
RP_D+2: R23.1, U9.4
RP_D+3: R32.1, U12.4
RP_D+4: R41.1, U15.4
RP_D+5: R50.1, U18.4
RP_D+6: R59.1, U21.4
RP_D+7: R68.1, U24.4
RP_D+8: R77.1, U27.4
RP_D+9: R86.1, U30.4
RP_D+10: R95.1, U33.4
RP_D+11: R104.1, U36.4
RP_D+12: R113.1, U39.4
RP_D+13: R122.1, U42.4
RP_D+14: R131.1, U45.4
RP_D+15: R140.1, U48.4
RP_D-: R11.1, U2.6
RP_D-1: R12.1, U6.6
RP_D-2: R22.1, U9.6
RP_D-3: R31.1, U12.6
RP_D-4: R40.1, U15.6
RP_D-5: R49.1, U18.6
RP_D-6: R58.1, U21.6
RP_D-7: R67.1, U24.6
RP_D-8: R76.1, U27.6
RP_D-9: R85.1, U30.6
RP_D-10: R94.1, U33.6
RP_D-11: R103.1, U36.6
RP_D-12: R112.1, U39.6
RP_D-13: R121.1, U42.6
RP_D-14: R130.1, U45.6
RP_D-15: R139.1, U48.6
RTS1/AUD_BCLK: J1.13, J1.50, U3.5
RTS1/AUD_BCLK1: J2.13, J2.50, U4.5
RTS1/AUD_BCLK2: J3.13, J3.50, U7.5
RTS1/AUD_BCLK3: J4.13, J4.50, U10.5
RTS1/AUD_BCLK4: J5.13, J5.50, U13.5
RTS1/AUD_BCLK5: J6.13, J6.50, U16.5
RTS1/AUD_BCLK6: J7.13, J7.50, U19.5
RTS1/AUD_BCLK7: J8.13, J8.50, U22.5
RTS1/AUD_BCLK8: J9.13, J9.50, U25.5
RTS1/AUD_BCLK9: J10.13, J10.50, U28.5
RTS1/AUD_BCLK10: J11.13, J11.50, U31.5
RTS1/AUD_BCLK11: J12.13, J12.50, U34.5
RTS1/AUD_BCLK12: J13.13, J13.50, U37.5
RTS1/AUD_BCLK13: J14.13, J14.50, U40.5
RTS1/AUD_BCLK14: J15.13, J15.50, U43.5
RTS1/AUD_BCLK15: J16.13, J16.50, U46.5
RX1: J1.19, U3.3
RX2: J2.19, U4.3
RX3: J3.19, U7.3
RX4: J4.19, U10.3
RX5: J5.19, U13.3
RX6: J6.19, U16.3
RX7: J7.19, U19.3
RX8: J8.19, U22.3
RX9: J9.19, U25.3
RX10: J10.19, U28.3
RX11: J11.19, U31.3
RX12: J12.19, U34.3
RX13: J13.19, U37.3
RX14: J14.19, U40.3
RX15: J15.19, U43.3
RX16: J16.19, U46.3
SCL: J1.14, U3.7
SCL1: J2.14, U4.7
SCL2: J3.14, U7.7
SCL3: J4.14, U10.7
SCL4: J5.14, U13.7
SCL5: J6.14, U16.7
SCL6: J7.14, U19.7
SCL7: J8.14, U22.7
SCL8: J9.14, U25.7
SCL9: J10.14, U28.7
SCL10: J11.14, U31.7
SCL11: J12.14, U34.7
SCL12: J13.14, U37.7
SCL13: J14.14, U40.7
SCL14: J15.14, U43.7
SCL15: J16.14, U46.7
SDA: J1.12, U3.6
SDA1: J2.12, U4.6
SDA2: J3.12, U7.6
SDA3: J4.12, U10.6
SDA4: J5.12, U13.6
SDA5: J6.12, U16.6
SDA6: J7.12, U19.6
SDA7: J8.12, U22.6
SDA8: J9.12, U25.6
SDA9: J10.12, U28.6
SDA10: J11.12, U31.6
SDA11: J12.12, U34.6
SDA12: J13.12, U37.6
SDA13: J14.12, U40.6
SDA14: J15.12, U43.6
SDA15: J16.12, U46.6
SDIO_DAT1/AUD_IN: J1.54, J1.66, U3.14
SDIO_DAT1/AUD_IN1: J2.54, J2.66, U4.14
SDIO_DAT1/AUD_IN2: J3.54, J3.66, U7.14
SDIO_DAT1/AUD_IN3: J4.54, J4.66, U10.14
SDIO_DAT1/AUD_IN4: J5.54, J5.66, U13.14
SDIO_DAT1/AUD_IN5: J6.54, J6.66, U16.14
SDIO_DAT1/AUD_IN6: J7.54, J7.66, U19.14
SDIO_DAT1/AUD_IN7: J8.54, J8.66, U22.14
SDIO_DAT1/AUD_IN8: J9.54, J9.66, U25.14
SDIO_DAT1/AUD_IN9: J10.54, J10.66, U28.14
SDIO_DAT1/AUD_IN10: J11.54, J11.66, U31.14
SDIO_DAT1/AUD_IN11: J12.54, J12.66, U34.14
SDIO_DAT1/AUD_IN12: J13.54, J13.66, U37.14
SDIO_DAT1/AUD_IN13: J14.54, J14.66, U40.14
SDIO_DAT1/AUD_IN14: J15.54, J15.66, U43.14
SDIO_DAT1/AUD_IN15: J16.54, J16.66, U46.14
SDIO_DAT2/AUD_OUT: J1.56, J1.68, U3.13
SDIO_DAT2/AUD_OUT1: J2.56, J2.68, U4.13
SDIO_DAT2/AUD_OUT2: J3.56, J3.68, U7.13
SDIO_DAT2/AUD_OUT3: J4.56, J4.68, U10.13
SDIO_DAT2/AUD_OUT4: J5.56, J5.68, U13.13
SDIO_DAT2/AUD_OUT5: J6.56, J6.68, U16.13
SDIO_DAT2/AUD_OUT6: J7.56, J7.68, U19.13
SDIO_DAT2/AUD_OUT7: J8.56, J8.68, U22.13
SDIO_DAT2/AUD_OUT8: J9.56, J9.68, U25.13
SDIO_DAT2/AUD_OUT9: J10.56, J10.68, U28.13
SDIO_DAT2/AUD_OUT10: J11.56, J11.68, U31.13
SDIO_DAT2/AUD_OUT11: J12.56, J12.68, U34.13
SDIO_DAT2/AUD_OUT12: J13.56, J13.68, U37.13
SDIO_DAT2/AUD_OUT13: J14.56, J14.68, U40.13
SDIO_DAT2/AUD_OUT14: J15.56, J15.68, U43.13
SDIO_DAT2/AUD_OUT15: J16.56, J16.68, U46.13
SPI_!CS1!/SDIO_DAT3/RX1: J2.20, J2.70, U4.12
SPI_!CS1!/SDIO_DAT3/RX2: J1.20, J1.70, U3.12
SPI_!CS1!/SDIO_DAT3/RX3: J3.20, J3.70, U7.12
SPI_!CS1!/SDIO_DAT3/RX4: J4.20, J4.70, U10.12
SPI_!CS1!/SDIO_DAT3/RX5: J5.20, J5.70, U13.12
SPI_!CS1!/SDIO_DAT3/RX6: J6.20, J6.70, U16.12
SPI_!CS1!/SDIO_DAT3/RX7: J7.20, J7.70, U19.12
SPI_!CS1!/SDIO_DAT3/RX8: J8.20, J8.70, U22.12
SPI_!CS1!/SDIO_DAT3/RX9: J9.20, J9.70, U25.12
SPI_!CS1!/SDIO_DAT3/RX10: J10.20, J10.70, U28.12
SPI_!CS1!/SDIO_DAT3/RX11: J11.20, J11.70, U31.12
SPI_!CS1!/SDIO_DAT3/RX12: J12.20, J12.70, U34.12
SPI_!CS1!/SDIO_DAT3/RX13: J13.20, J13.70, U37.12
SPI_!CS1!/SDIO_DAT3/RX14: J14.20, J14.70, U40.12
SPI_!CS1!/SDIO_DAT3/RX15: J15.20, J15.70, U43.12
SPI_!CS1!/SDIO_DAT3/RX16: J16.20, J16.70, U46.12
SPI_!CS!/GPIO1: J2.55, J2.73, U4.32
SPI_!CS!/GPIO2: J3.55, J3.73, U7.32
SPI_!CS!/GPIO3: J4.55, J4.73, U10.32
SPI_!CS!/GPIO4: J5.55, J5.73, U13.32
SPI_!CS!/GPIO5: J1.55, J1.73, U3.32
SPI_!CS!/GPIO6: J6.55, J6.73, U16.32
SPI_!CS!/GPIO7: J7.55, J7.73, U19.32
SPI_!CS!/GPIO8: J8.55, J8.73, U22.32
SPI_!CS!/GPIO9: J9.55, J9.73, U25.32
SPI_!CS!/GPIO10: J10.55, J10.73, U28.32
SPI_!CS!/GPIO11: J11.55, J11.73, U31.32
SPI_!CS!/GPIO12: J12.55, J12.73, U34.32
SPI_!CS!/GPIO13: J13.55, J13.73, U37.32
SPI_!CS!/GPIO14: J14.55, J14.73, U40.32
SPI_!CS!/GPIO15: J15.55, J15.73, U43.32
SPI_!CS!/GPIO16: J16.55, J16.73, U46.32
SPI_CIPO1/SDIO_DAT0: J1.64, U3.15
SPI_CIPO1/SDIO_DAT1: J2.64, U4.15
SPI_CIPO1/SDIO_DAT2: J3.64, U7.15
SPI_CIPO1/SDIO_DAT3: J4.64, U10.15
SPI_CIPO1/SDIO_DAT4: J5.64, U13.15
SPI_CIPO1/SDIO_DAT5: J6.64, U16.15
SPI_CIPO1/SDIO_DAT6: J7.64, U19.15
SPI_CIPO1/SDIO_DAT7: J8.64, U22.15
SPI_CIPO1/SDIO_DAT8: J9.64, U25.15
SPI_CIPO1/SDIO_DAT9: J10.64, U28.15
SPI_CIPO1/SDIO_DAT10: J11.64, U31.15
SPI_CIPO1/SDIO_DAT11: J12.64, U34.15
SPI_CIPO1/SDIO_DAT12: J13.64, U37.15
SPI_CIPO1/SDIO_DAT13: J14.64, U40.15
SPI_CIPO1/SDIO_DAT14: J15.64, U43.15
SPI_CIPO1/SDIO_DAT15: J16.64, U46.15
SPI_CIPO/GPIO1: J2.48, J2.61, U4.31
SPI_CIPO/GPIO2: J3.48, J3.61, U7.31
SPI_CIPO/GPIO3: J4.48, J4.61, U10.31
SPI_CIPO/GPIO4: J1.48, J1.61, U3.31
SPI_CIPO/GPIO5: J5.48, J5.61, U13.31
SPI_CIPO/GPIO6: J6.48, J6.61, U16.31
SPI_CIPO/GPIO7: J7.48, J7.61, U19.31
SPI_CIPO/GPIO8: J8.48, J8.61, U22.31
SPI_CIPO/GPIO9: J9.48, J9.61, U25.31
SPI_CIPO/GPIO10: J10.48, J10.61, U28.31
SPI_CIPO/GPIO11: J11.48, J11.61, U31.31
SPI_CIPO/GPIO12: J12.48, J12.61, U34.31
SPI_CIPO/GPIO13: J13.48, J13.61, U37.31
SPI_CIPO/GPIO14: J14.48, J14.61, U40.31
SPI_CIPO/GPIO15: J15.48, J15.61, U43.31
SPI_CIPO/GPIO16: J16.48, J16.61, U46.31
SPI_COPI1/SDIO_CMD: J1.62, U3.18
SPI_COPI1/SDIO_CMD1: J2.62, U4.18
SPI_COPI1/SDIO_CMD2: J3.62, U7.18
SPI_COPI1/SDIO_CMD3: J4.62, U10.18
SPI_COPI1/SDIO_CMD4: J5.62, U13.18
SPI_COPI1/SDIO_CMD5: J6.62, U16.18
SPI_COPI1/SDIO_CMD6: J7.62, U19.18
SPI_COPI1/SDIO_CMD7: J8.62, U22.18
SPI_COPI1/SDIO_CMD8: J9.62, U25.18
SPI_COPI1/SDIO_CMD9: J10.62, U28.18
SPI_COPI1/SDIO_CMD10: J11.62, U31.18
SPI_COPI1/SDIO_CMD11: J12.62, U34.18
SPI_COPI1/SDIO_CMD12: J13.62, U37.18
SPI_COPI1/SDIO_CMD13: J14.62, U40.18
SPI_COPI1/SDIO_CMD14: J15.62, U43.18
SPI_COPI1/SDIO_CMD15: J16.62, U46.18
SPI_COPI/GPIO1: J2.59, J2.69, U4.35
SPI_COPI/GPIO2: J3.59, J3.69, U7.35
SPI_COPI/GPIO3: J4.59, J4.69, U10.35
SPI_COPI/GPIO4: J5.59, J5.69, U13.35
SPI_COPI/GPIO5: J6.59, J6.69, U16.35
SPI_COPI/GPIO6: J7.59, J7.69, U19.35
SPI_COPI/GPIO7: J1.59, J1.69, U3.35
SPI_COPI/GPIO8: J8.59, J8.69, U22.35
SPI_COPI/GPIO9: J9.59, J9.69, U25.35
SPI_COPI/GPIO10: J10.59, J10.69, U28.35
SPI_COPI/GPIO11: J11.59, J11.69, U31.35
SPI_COPI/GPIO12: J12.59, J12.69, U34.35
SPI_COPI/GPIO13: J13.59, J13.69, U37.35
SPI_COPI/GPIO14: J14.59, J14.69, U40.35
SPI_COPI/GPIO15: J15.59, J15.69, U43.35
SPI_COPI/GPIO16: J16.59, J16.69, U46.35
SPI_SCK1/SDIO_CLK: J1.60, U3.17
SPI_SCK1/SDIO_CLK1: J2.60, U4.17
SPI_SCK1/SDIO_CLK2: J3.60, U7.17
SPI_SCK1/SDIO_CLK3: J4.60, U10.17
SPI_SCK1/SDIO_CLK4: J5.60, U13.17
SPI_SCK1/SDIO_CLK5: J6.60, U16.17
SPI_SCK1/SDIO_CLK6: J7.60, U19.17
SPI_SCK1/SDIO_CLK7: J8.60, U22.17
SPI_SCK1/SDIO_CLK8: J9.60, U25.17
SPI_SCK1/SDIO_CLK9: J10.60, U28.17
SPI_SCK1/SDIO_CLK10: J11.60, U31.17
SPI_SCK1/SDIO_CLK11: J12.60, U34.17
SPI_SCK1/SDIO_CLK12: J13.60, U37.17
SPI_SCK1/SDIO_CLK13: J14.60, U40.17
SPI_SCK1/SDIO_CLK14: J15.60, U43.17
SPI_SCK1/SDIO_CLK15: J16.60, U46.17
SPI_SCK/GPIO1: J2.57, J2.71, U4.34
SPI_SCK/GPIO2: J3.57, J3.71, U7.34
SPI_SCK/GPIO3: J4.57, J4.71, U10.34
SPI_SCK/GPIO4: J5.57, J5.71, U13.34
SPI_SCK/GPIO5: J6.57, J6.71, U16.34
SPI_SCK/GPIO6: J1.57, J1.71, U3.34
SPI_SCK/GPIO7: J7.57, J7.71, U19.34
SPI_SCK/GPIO8: J8.57, J8.71, U22.34
SPI_SCK/GPIO9: J9.57, J9.71, U25.34
SPI_SCK/GPIO10: J10.57, J10.71, U28.34
SPI_SCK/GPIO11: J11.57, J11.71, U31.34
SPI_SCK/GPIO12: J12.57, J12.71, U34.34
SPI_SCK/GPIO13: J13.57, J13.71, U37.34
SPI_SCK/GPIO14: J14.57, J14.71, U40.34
SPI_SCK/GPIO15: J15.57, J15.71, U43.34
SPI_SCK/GPIO16: J16.57, J16.71, U46.34
SWDCK: J1.21, U3.24
SWDCK1: J2.21, U4.24
SWDCK2: J3.21, U7.24
SWDCK3: J4.21, U10.24
SWDCK4: J5.21, U13.24
SWDCK5: J6.21, U16.24
SWDCK6: J7.21, U19.24
SWDCK7: J8.21, U22.24
SWDCK8: J9.21, U25.24
SWDCK9: J10.21, U28.24
SWDCK10: J11.21, U31.24
SWDCK11: J12.21, U34.24
SWDCK12: J13.21, U37.24
SWDCK13: J14.21, U40.24
SWDCK14: J15.21, U43.24
SWDCK15: J16.21, U46.24
SWDIO: J1.23, U3.25
SWDIO1: J2.23, U4.25
SWDIO2: J3.23, U7.25
SWDIO3: J4.23, U10.25
SWDIO4: J5.23, U13.25
SWDIO5: J6.23, U16.25
SWDIO6: J7.23, U19.25
SWDIO7: J8.23, U22.25
SWDIO8: J9.23, U25.25
SWDIO9: J10.23, U28.25
SWDIO10: J11.23, U31.25
SWDIO11: J12.23, U34.25
SWDIO12: J13.23, U37.25
SWDIO13: J14.23, U40.25
SWDIO14: J15.23, U43.25
SWDIO15: J16.23, U46.25
TX1: J1.17, U3.2
TX2: J2.17, U4.2
TX3: J3.17, U7.2
TX4: J4.17, U10.2
TX5: J5.17, U13.2
TX6: J6.17, U16.2
TX7: J7.17, U19.2
TX8: J8.17, U22.2
TX9: J9.17, U25.2
TX10: J10.17, U28.2
TX11: J11.17, U31.2
TX12: J12.17, U34.2
TX13: J13.17, U37.2
TX14: J14.17, U40.2
TX15: J15.17, U43.2
TX16: J16.17, U46.2
USBHOST_D+: J1.35, U2.2
USBHOST_D+1: J2.35, U6.2
USBHOST_D+2: J3.35, U9.2
USBHOST_D+3: J4.35, U12.2
USBHOST_D+4: J5.35, U15.2
USBHOST_D+5: J6.35, U18.2
USBHOST_D+6: J7.35, U21.2
USBHOST_D+7: J8.35, U24.2
USBHOST_D+8: J9.35, U27.2
USBHOST_D+9: J10.35, U30.2
USBHOST_D+10: J11.35, U33.2
USBHOST_D+11: J12.35, U36.2
USBHOST_D+12: J13.35, U39.2
USBHOST_D+13: J14.35, U42.2
USBHOST_D+14: J15.35, U45.2
USBHOST_D+15: J16.35, U48.2
USBHOST_D-: J1.37, U2.8
USBHOST_D-1: J2.37, U6.8
USBHOST_D-2: J3.37, U9.8
USBHOST_D-3: J4.37, U12.8
USBHOST_D-4: J5.37, U15.8
USBHOST_D-5: J6.37, U18.8
USBHOST_D-6: J7.37, U21.8
USBHOST_D-7: J8.37, U24.8
USBHOST_D-8: J9.37, U27.8
USBHOST_D-9: J10.37, U30.8
USBHOST_D-10: J11.37, U33.8
USBHOST_D-11: J12.37, U36.8
USBHOST_D-12: J13.37, U39.8
USBHOST_D-13: J14.37, U42.8
USBHOST_D-14: J15.37, U45.8
USBHOST_D-15: J16.37, U48.8
USB_D+: J1.3, U2.3
USB_D+1: J2.3, U6.3
USB_D+2: J3.3, U9.3
USB_D+3: J4.3, U12.3
USB_D+4: J5.3, U15.3
USB_D+5: J6.3, U18.3
USB_D+6: J7.3, U21.3
USB_D+7: J8.3, U24.3
USB_D+8: J9.3, U27.3
USB_D+9: J10.3, U30.3
USB_D+10: J11.3, U33.3
USB_D+11: J12.3, U36.3
USB_D+12: J13.3, U39.3
USB_D+13: J14.3, U42.3
USB_D+14: J15.3, U45.3
USB_D+15: J16.3, U48.3
USB_D-: J1.5, U2.7
USB_D-1: J2.5, U6.7
USB_D-2: J3.5, U9.7
USB_D-3: J4.5, U12.7
USB_D-4: J5.5, U15.7
USB_D-5: J6.5, U18.7
USB_D-6: J7.5, U21.7
USB_D-7: J8.5, U24.7
USB_D-8: J9.5, U27.7
USB_D-9: J10.5, U30.7
USB_D-10: J11.5, U33.7
USB_D-11: J12.5, U36.7
USB_D-12: J13.5, U39.7
USB_D-13: J14.5, U42.7
USB_D-14: J15.5, U45.7
USB_D-15: J16.5, U48.7
USB_MUX_SIG: R5.2, R18.2, U2.1
USB_MUX_SIG1: R16.2, R17.2, U6.1
USB_MUX_SIG2: R26.2, R27.2, U9.1
USB_MUX_SIG3: R35.2, R36.2, U12.1
USB_MUX_SIG4: R44.2, R45.2, U15.1
USB_MUX_SIG5: R53.2, R54.2, U18.1
USB_MUX_SIG6: R62.2, R63.2, U21.1
USB_MUX_SIG7: R71.2, R72.2, U24.1
USB_MUX_SIG8: R80.2, R81.2, U27.1
USB_MUX_SIG9: R89.2, R90.2, U30.1
USB_MUX_SIG10: R98.2, R99.2, U33.1
USB_MUX_SIG11: R107.2, R108.2, U36.1
USB_MUX_SIG12: R116.2, R117.2, U39.1
USB_MUX_SIG13: R125.2, R126.2, U42.1
USB_MUX_SIG14: R134.2, R135.2, U45.1
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
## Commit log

2020-11-13 Add ignore. Update prod_id on xtal. Remove backup files.
2020-11-16 Add pullup to flash
2020-11-23 Update FP to RPi recommended
2020-12-08 Adding production files
2020-12-08 Update USB mux prod ID
2020-12-29 Update silk
2020-12-31 Rename nets to match MicroMod nomenclature
2021-01-22 Update Schematic (PDF) and Add Dimensions in BRD File
    - regenerate schematic with updated nets based on MicroMod nomenclature
    - Add board measurements in dimensions layer
2021-03-23 Remove Outdated Files
    Removing outdated datasheet, the latest can be found from Raspberry Pi =)
